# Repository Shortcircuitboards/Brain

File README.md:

# -//Brain
OSD PCB wit Sensors and usefull stuff for the FPV Rover

The Rover-Brain is complete PDB with integratetd OSD, BEC, Current Sensor, Voltage Sensor, RSSI Filter, LC Filter, and 3 Step Switch. 
It´s to keep the FPV-Rover Clean of a wire mess and to have all necessary information of your onboard system in your Video-Downlink.

I used a Mashup of the Legendary E-OSD and put some sensors and other usefull parts on one PCB. It fit´s for 2S and 3S.

The Development, Schematic and Software of the 3-Way Switch was done by JReise http://jreise.de/ (more software and Infos)
The Development, Schematic and Software of the E-OSD was done by ?? Arrgh i dont know ^^

For Setting it up You just need an USBASP to flash the OSD Firmware and the .HEX file of the AtTiny13 which is in use as an 3-Step Swicht (for flashing the pure .hex file i Use Burn-O-Mat) 
Here is the software for the attiny13: http://jreise.de/RCUSB/Daten/2-Stufen-RC-Schalter.zip  all rights by JReise !!!  Since his page is just accessible over waybackmachine.com i Uploaded the neccessary hex file to flash the attiny13

For the OSD i use the G-OSD GUI which is awseome and easy to handel !

You can manually set up the Voltage Divider with the Potentiometer P1 and the output of the Currentsensor with P2, so you can easyily adjust it to exactly that value that you need.

Pinout Legend (will be countinued later):
1 = ESC1 PWM
2 =
3 = 
4 = 
5 =
6 =
7 =
8 =
9 =
10=
11=
12=
13=
14=
15=
16=
17=
18= ESC2 PWM

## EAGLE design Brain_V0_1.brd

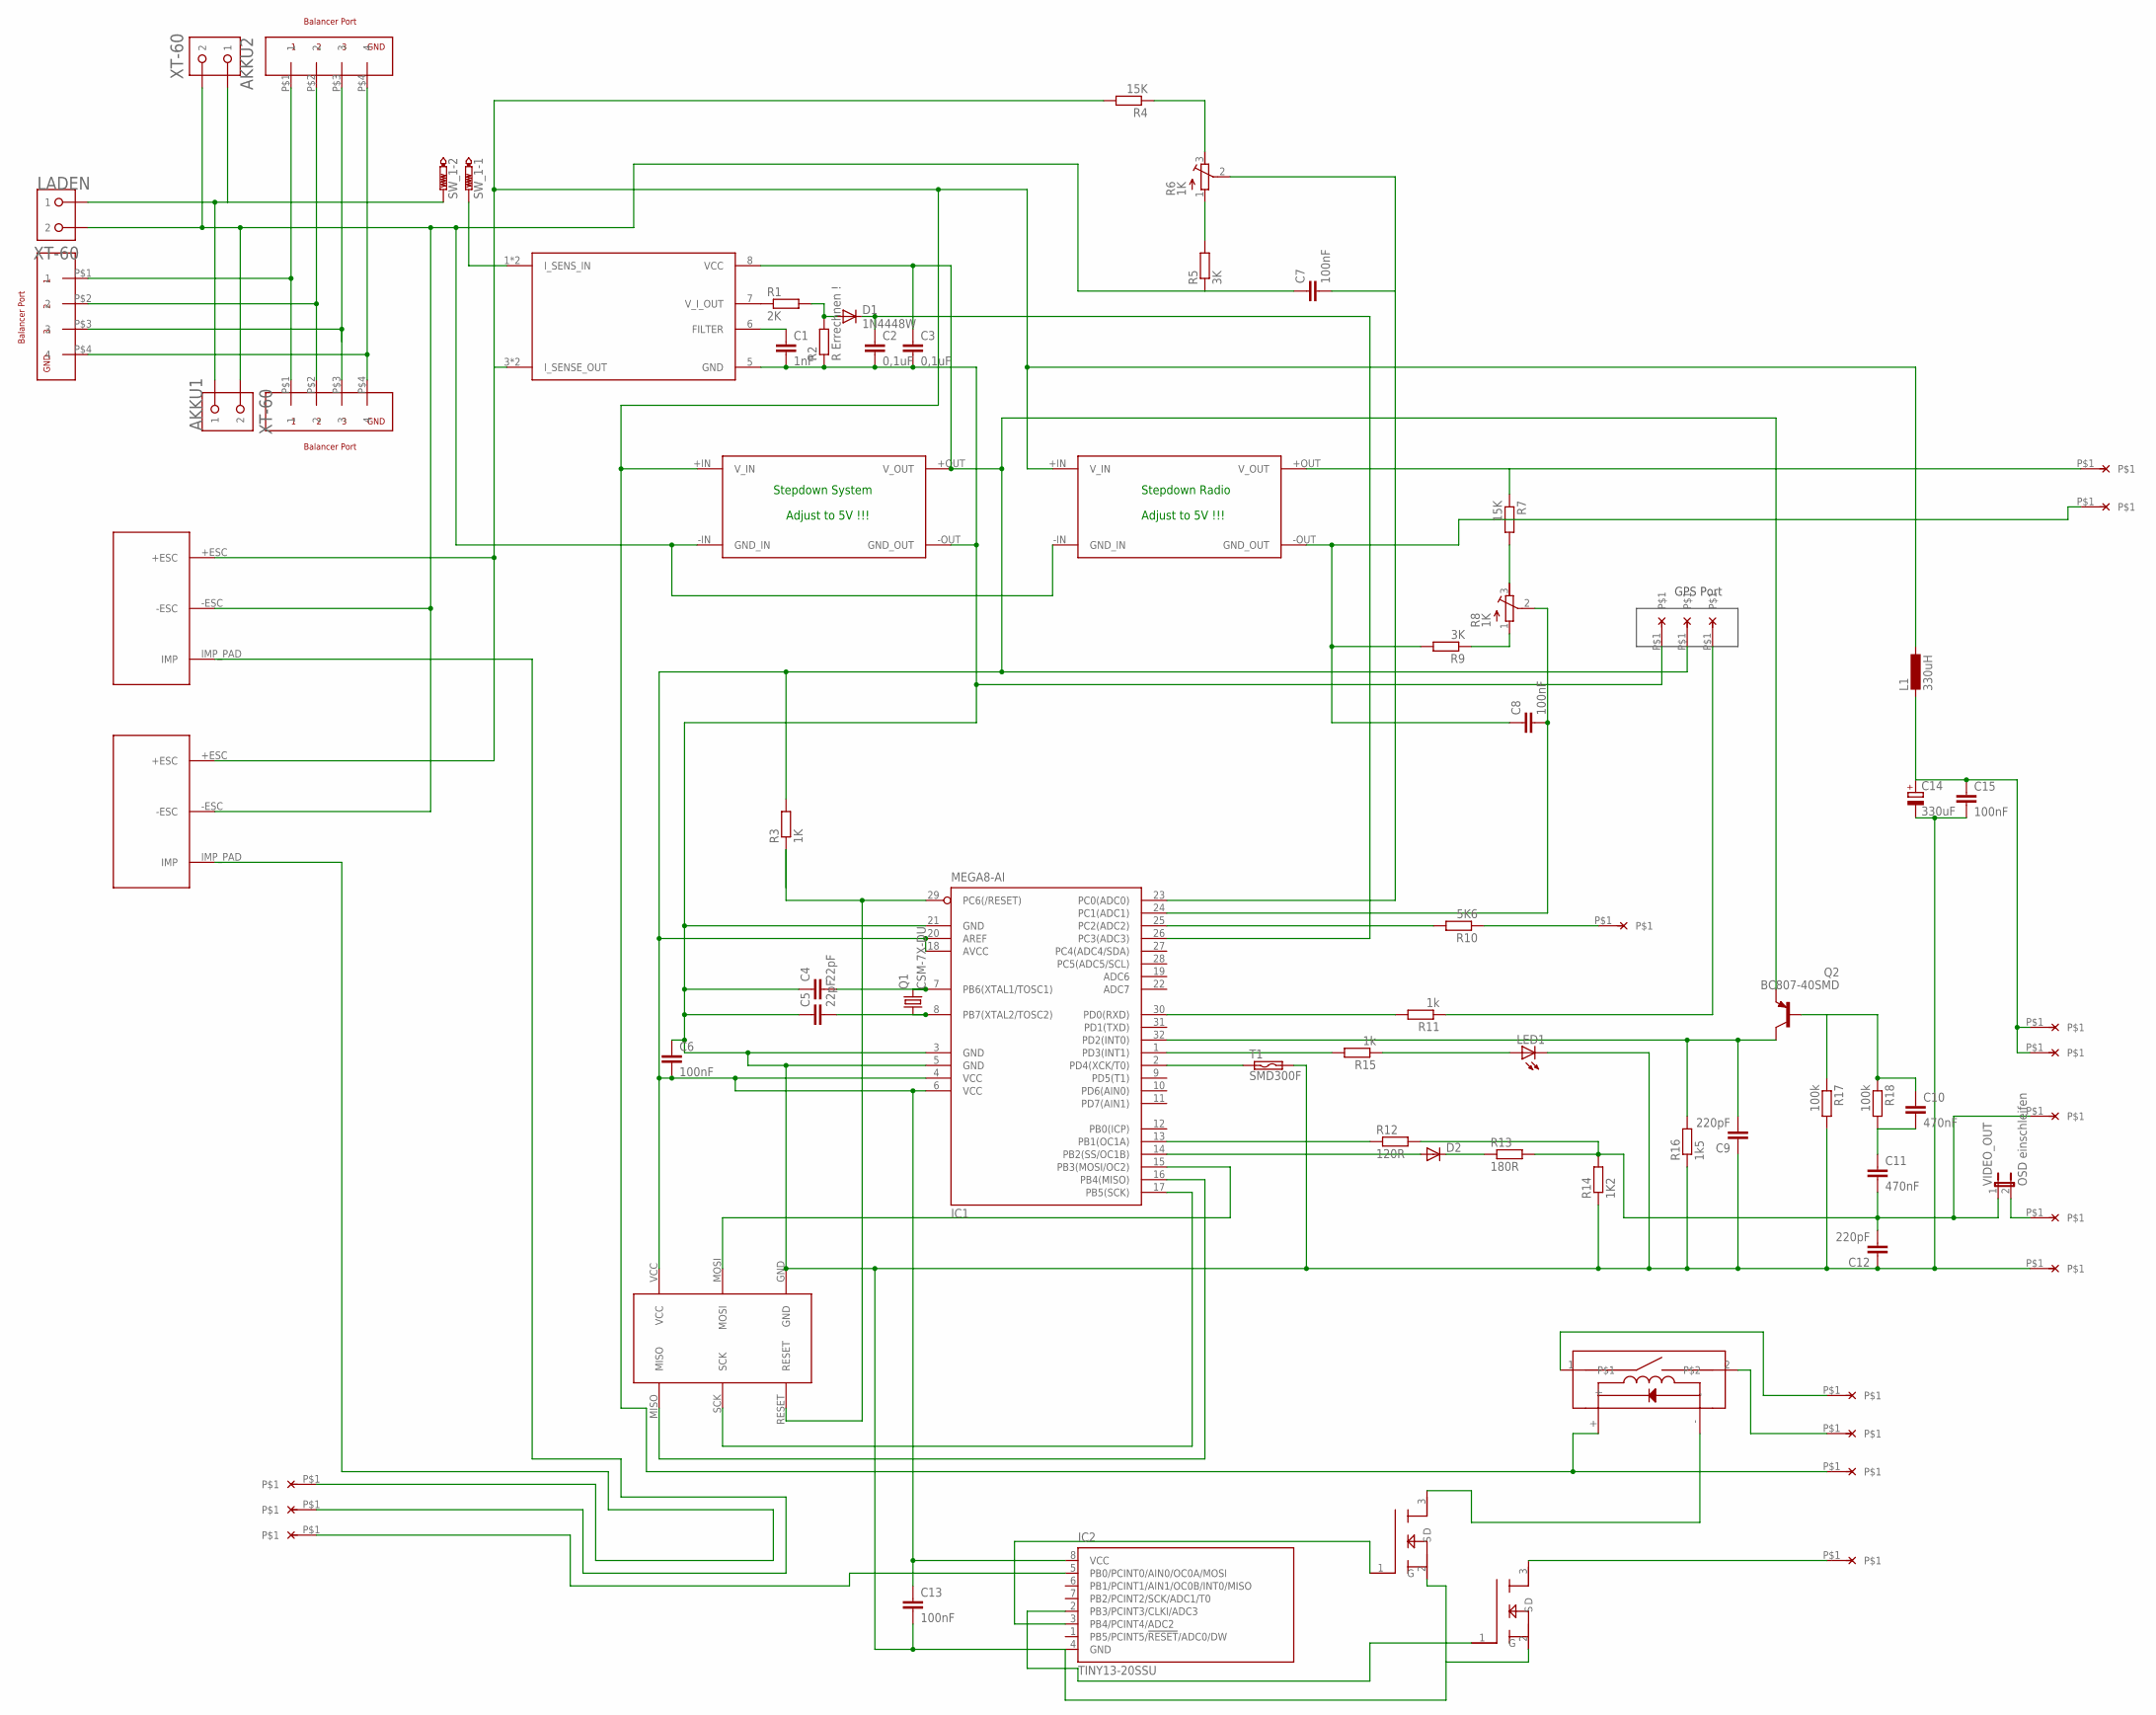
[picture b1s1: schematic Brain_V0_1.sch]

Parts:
5V_GPS: LöTPAD_KLEIN
AKKU1, AKKU2: XT-60
BALANCER_1, BALANCER_2: BALANCER_3S
BALANCE_OUT: BALANCER_3S
BEC+: LöTPAD_KLEIN
BEC-: LöTPAD_KLEIN
C1: 1nF; C0603K
C2, C3: 0,1uF; C0603K
C4, C5: 22pF; C0603K
C6, C7, C8, C13, C15: 100nF; C0603K
C9, C12: 220pF; C0603K
C10, C11: 470nF; C1206
C14: 330uF; 153CLV-0807
CAMERA_VIDEO: LöTPAD_KLEIN
CH1_IN, CH2_IN, CH3_IN: LöTPAD_KLEIN
D1: 1N4448W; SOD523
D2: DIODE-DO-214AC; DO-214AC
ESC1, ESC2: MOT_CONNECTOR
FILTER: LöTPAD_KLEIN
FILTER_: LöTPAD_KLEIN
GND_GPS: LöTPAD_KLEIN
GND_VIDEO: LöTPAD_KLEIN
IC1: MEGA8-AI; TQFP32-08
IC2: TINY13-20SSU; 8S1
IR_GND: LöTPAD_KLEIN
IR_VCC: LöTPAD_KLEIN
L1: 330uH; POWER-CHOKE_WE-TPC
LADEN: XT-60
LED1: LEDCHIP-LED0603; CHIP-LED0603
Q1: CSM-7X-DU
Q2: BC807-40SMD; SOT23-BEC
R1: 2K; R0603
R2: R Errechnen !; R0603
R3: 1K; R0603
R4, R7: 15K; R0603
R5, R9: 3K; R0603
R6, R8: 1K; RTRIM3103
R10: 5K6; R0603
R11, R15: 1k; R0603
R12: 120R; R0603
R13: 180R; R0603
R14: 1K2; R0603
R16: 1k5; R0603
R17, R18: 100k; R0603
RSSI_IN: LöTPAD_KLEIN
RX_GPS: LöTPAD_KLEIN
STEPDOWN_RADIO: STEPDOWN_MINI; STEPDOWN_SMALL
STEPDOWN_SYSTEM: STEPDOWN_MINI; STEPDOWN_SMALL
SW_1: PTR2; P2-38-17
T1: SMD300F; SMD050F
U$1: REED-RELAIS
U$2, U$5: IRLM2502; SOT23
U$3: I_SENSE_IC; SOIC8
U$4: ICSP_6P
VCC_CAM: LöTPAD_KLEIN
VCC_VTX: LöTPAD_KLEIN
VIDEO: LöTPAD_KLEIN
VIDEO_OUT: OSD einschleifen; JP1

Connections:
unnamed: AKKU1.BATT (1), AKKU2.BATT (1), LADEN.BATT (1), SW_1.TP-2
unnamed: AKKU1.GND (2), AKKU2.GND (2), C7.1, ESC1.-ESC, ESC2.-ESC, LADEN.GND (2), R5.1, STEPDOWN_RADIO.-IN (GND_IN), STEPDOWN_SYSTEM.-IN (GND_IN)
unnamed: BALANCER_1.P$1 (1), BALANCER_2.P$1 (1), BALANCE_OUT.P$1 (1)
unnamed: BALANCER_1.P$2 (2), BALANCER_2.P$2 (2), BALANCE_OUT.P$2 (2)
unnamed: BALANCER_1.P$4 (4), BALANCER_2.P$4 (4), BALANCE_OUT.P$4 (4)
unnamed: SW_1.TP-1, U$3.1 (I_SENS_IN), U$3.2 (I_SENS_IN)
unnamed: 5V_GPS.P$1, C3.1, C6.2, C13.1, IC1.4 (VCC), IC1.6 (VCC), IC1.18 (AVCC), IC1.20 (AREF), IC2.8 (VCC), Q2.E, R3.2, STEPDOWN_SYSTEM.+OUT (V_OUT), U$3.8 (VCC), U$4.VCC
unnamed: C4.2, IC1.7 (PB6(XTAL1/TOSC1)), Q1.2
unnamed: C1.1, U$3.6 (FILTER)
unnamed: R1.1, U$3.7 (V_I_OUT)
unnamed: D1.A, R1.2, R2.2
unnamed: C2.1, D1.C, IC1.26 (PC3(ADC3))
unnamed: FILTER_.P$1, U$1.2
unnamed: C5.2, IC1.8 (PB7(XTAL2/TOSC2)), Q1.1
unnamed: IC1.29 (PC6(/RESET)), R3.1, U$4.RESET
unnamed: IC1.15 (PB3(MOSI/OC2)), U$4.MOSI
unnamed: IC1.17 (PB5(SCK)), U$4.SCK
unnamed: R4.1, R6.3 (E)
unnamed: IC1.16 (PB4(MISO)), U$4.MISO
unnamed: R5.2, R6.1 (A)
unnamed: VIDEO.P$1, VIDEO_OUT.2
unnamed: C7.2, IC1.23 (PC0(ADC0)), R6.2 (S)
unnamed: R7.2, R8.3 (E)
unnamed: R8.1 (A), R9.1
unnamed: BEC-.P$1, C8.1, R9.2, STEPDOWN_RADIO.-OUT (GND_OUT)
unnamed: C8.2, IC1.24 (PC1(ADC1)), R8.2 (S)
unnamed: IC1.25 (PC2(ADC2)), R10.2
unnamed: R10.1, RSSI_IN.P$1
unnamed: IC1.30 (PD0(RXD)), R11.2
unnamed: R11.1, RX_GPS.P$1
unnamed: IC1.2 (PD4(XCK/T0)), T1.1
unnamed: IC1.13 (PB1(OC1A)), R12.1
unnamed: C11.2, C12.2, CAMERA_VIDEO.P$1, R12.2, R13.2, R14.2, VIDEO_OUT.1
unnamed: D2.A, IC1.14 (PB2(SS/OC1B))
unnamed: D2.C, R13.1
unnamed: IC1.1 (PD3(INT1)), R15.2
unnamed: LED1.A, R15.1
unnamed: CH1_IN.P$1, ESC2.IMP_PAD (IMP)
unnamed: CH2_IN.P$1, ESC1.IMP_PAD (IMP)
unnamed: CH3_IN.P$1, IC2.5 (PB0/PCINT0/AIN0/OC0A/MOSI)
unnamed: FILTER.P$1, U$1.1
unnamed: ESC1.+ESC, ESC2.+ESC, IR_VCC.P$1, L1.1, R4.2, STEPDOWN_RADIO.+IN (V_IN), STEPDOWN_SYSTEM.+IN (V_IN), U$1.+, U$3.3 (I_SENSE_OUT), U$3.4 (I_SENSE_OUT)
unnamed: C9.2, IC1.32 (PD2(INT0)), Q2.C, R16.2
unnamed: C10.1, Q2.B, R17.1, R18.1
unnamed: BALANCER_1.P$3 (3), BALANCER_2.P$3 (3), BALANCE_OUT.P$3 (3)
unnamed: C10.2, C11.1, R18.2
unnamed: IC2.3 (PB4/PCINT4/ADC2), U$2.1 (G)
unnamed: IC2.2 (PB3/PCINT3/CLKI/ADC3), U$5.1 (G)
unnamed: U$1.-, U$2.3 (D)
unnamed: IR_GND.P$1, U$5.3 (D)
unnamed: BEC+.P$1, R7.1, STEPDOWN_RADIO.+OUT (V_OUT)
unnamed: C14.+, C15.1, L1.2, VCC_CAM.P$1, VCC_VTX.P$1
unnamed: C1.2, C2.2, C3.2, C4.1, C5.1, C6.1, C9.1, C12.1, C13.2, C14.-, C15.2, GND_GPS.P$1, GND_VIDEO.P$1, IC1.3 (GND), IC1.5 (GND), IC1.21 (GND), IC2.4 (GND), LED1.C, R2.1, R14.1, R16.1, R17.2, STEPDOWN_SYSTEM.-OUT (GND_OUT), T1.2, U$2.2 (S), U$3.5 (GND), U$4.GND, U$5.2 (S)

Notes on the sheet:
Stepdown System
Stepdown Radio
Adjust to 5V !!!
GPS Port

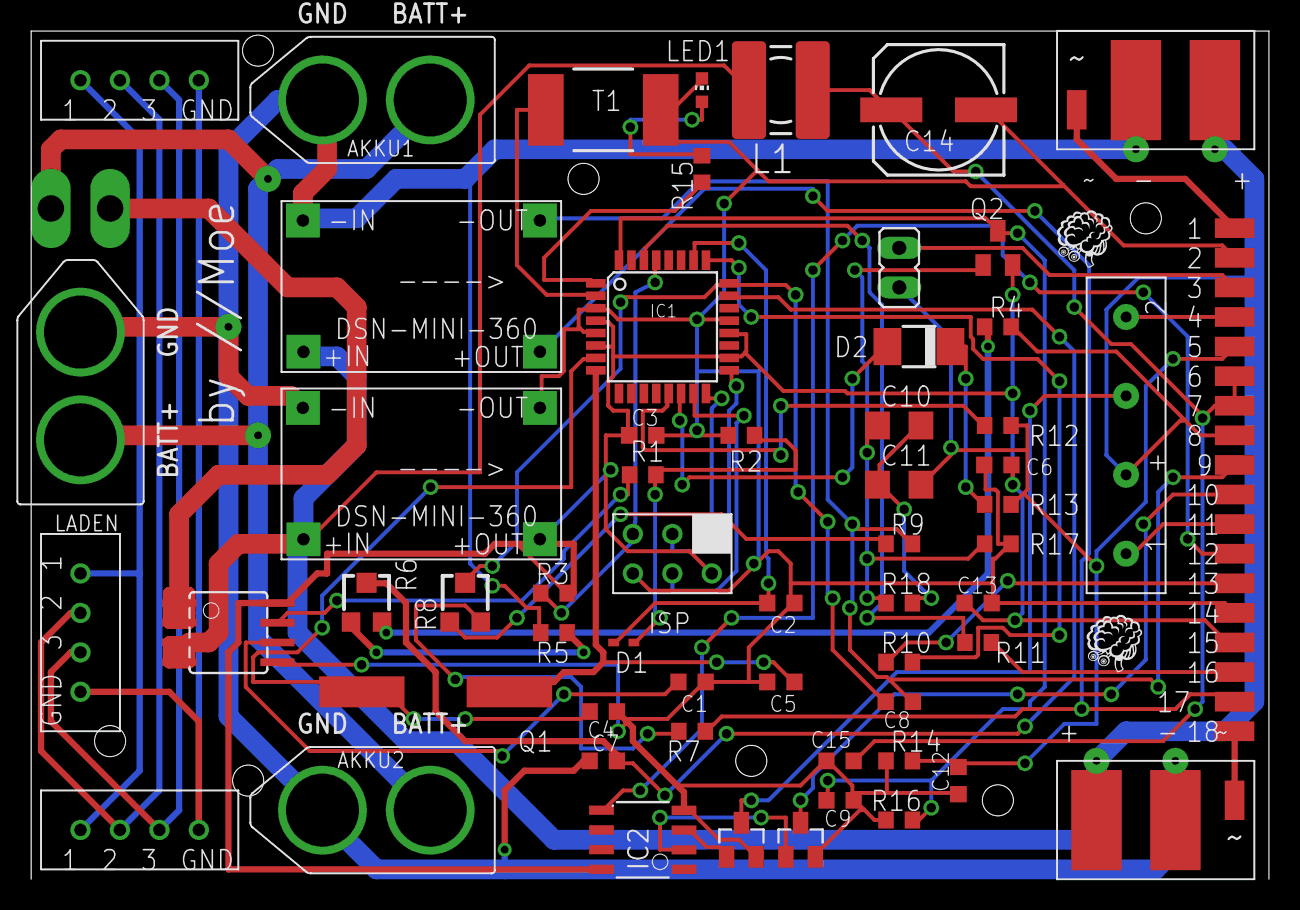
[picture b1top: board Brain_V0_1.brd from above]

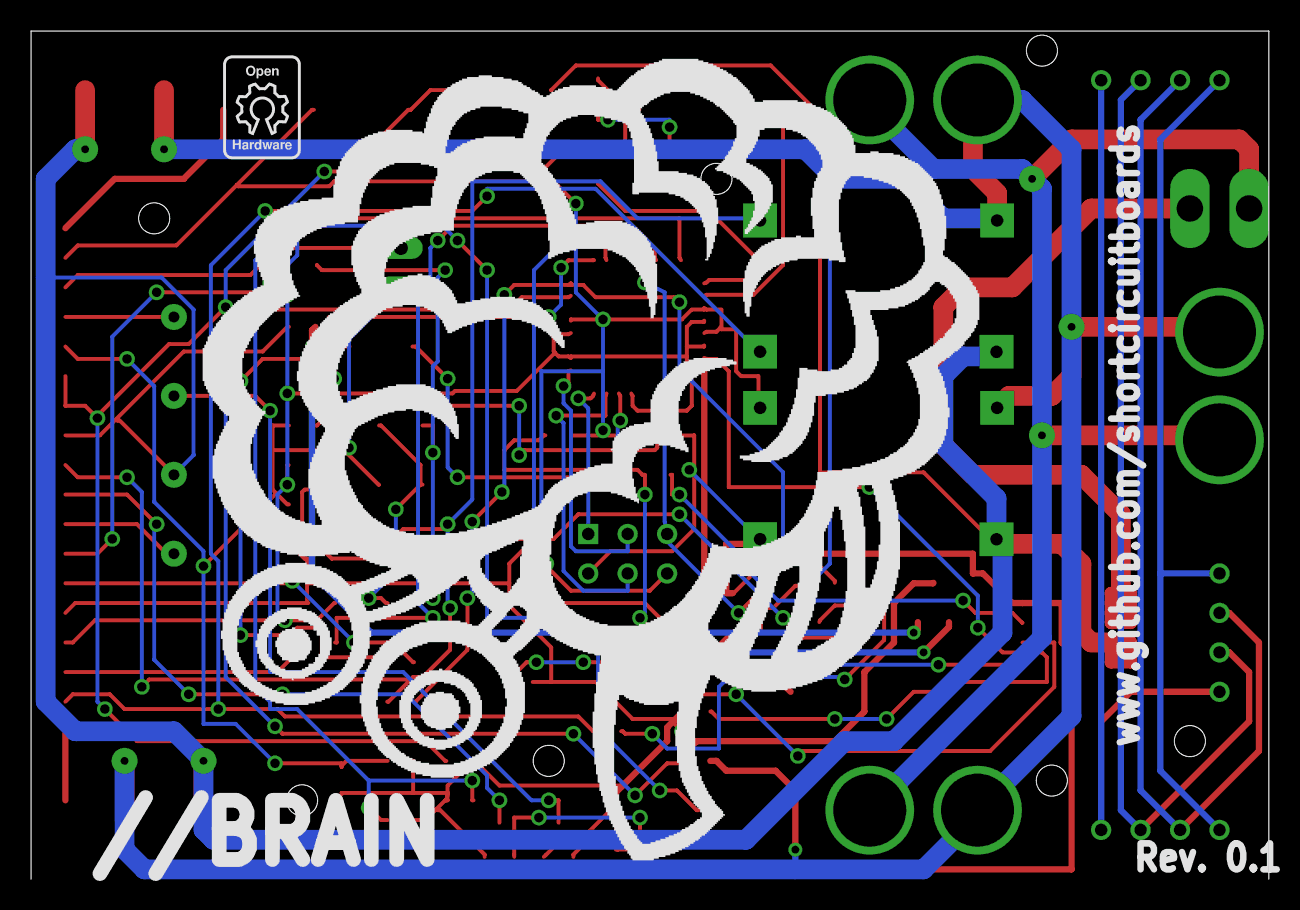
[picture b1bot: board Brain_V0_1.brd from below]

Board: 2 copper layers, 79.7 x 54.6 mm, 81 parts (2 on the bottom side), 53 nets.

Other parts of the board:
E$1, E$2: BRAINLOGO
E$3: BRAINLOGO_BIG
E$4: OPEN_HARDWARE_SMALL

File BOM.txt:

Partlist

Exported from Brain_V0_1.brd at 12.01.2016 13:22:20

EAGLE Version 6.3.0 Copyright (c) 1988-2012 CadSoft

Assembly variant: 

Part            Value            Package            Library                Position (mm)         Orientation


AKKU1           XT-60            XT-60              RoboJackets-Connectors (29.845 75.565)       R90
AKKU2           XT-60            XT-60              RoboJackets-Connectors (29.845 29.845)       R90
C1              1nF              C0603K             resistor               (42.545 38.1)         R0
C2              0,1uF            C0603K             resistor               (48.26 43.18)         R0
C3              0,1uF            C0603K             resistor               (39.37 53.975)        R0
C4              22pF             C0603K             rcl                    (36.83 36.195)        R180
C5              22pF             C0603K             rcl                    (48.26 38.1)          R0
C6              100nF            C0603K             rcl                    (62.23 52.07)         R0
C7              100nF            C0603K             rcl                    (36.83 33.02)         R0
C8              100nF            C0603K             rcl                    (55.88 36.83)         R180
C9              220pF            C0603K             rcl                    (52.07 30.48)         R180
C10             470nF            C1206              rcl                    (55.88 54.61)         R0
C11             470nF            C1206              rcl                    (55.88 50.8)          R0
C12             220pF            C0603K             rcl                    (59.69 31.75)         R90
C13             100nF            C0603K             rcl                    (60.96 43.18)         R0
C14             330uF            153CLV-0807        rcl                    (58.42 74.93)         R180
C15             100nF            C0603K             rcl                    (52.07 33.02)         R180
D1              1N4448W          SOD523             diode                  (38.1 40.64)          R0
D2                               DO-214AC           diode                  (57.15 59.69)         R180
IC1             MEGA8-AI         TQFP32-08          atmel                  (40.64 60.96)         R0
IC2             TINY13-20SSU     8S1                atmel                  (39.37 27.94)         R90
L1              330uH            POWER-CHOKE_WE-TPC rcl                    (48.26 76.2)          R90
LADEN           XT-60            XT-60              RoboJackets-Connectors (3.175 49.53)         R0
LED1                             CHIP-LED0603       led                    (43.18 76.2)          R0
Q1              CSM-7X-DU        CSM-7X-DU          crystal 16 mhz               (26.035 37.465)       R180
Q2              BC807-40SMD      SOT23-BEC          transistor-pnp         (62.23 66.04)         R0
R1              2K               R0603              resistor               (39.37 51.435)        R0
R2              R Errechnen !    R0603              resistor               (45.72 53.975)        R0
R3              1K               R0603              rcl                    (33.655 43.815)       R0
R4              15K              R0603              rcl                    (62.23 60.96)         R0
R5              3K               R0603              rcl                    (33.655 41.275)       R0
R6              1K               RTRIM3103          rcl                    (21.59 43.18)         R0
R7              15K              R0603              rcl                    (42.545 34.925)       R180
R8              1K               RTRIM3103          rcl                    (27.94 43.18)         R0
R9              3K               R0603              rcl                    (55.88 46.99)         R0
R10             5K6              R0603              rcl                    (55.88 39.37)         R0
R11             1k               R0603              rcl                    (60.96 40.64)         R180
R12             120R             R0603              rcl                    (62.23 54.61)         R0
R13             180R             R0603              rcl                    (62.23 49.53)         R0
R14             1K2              R0603              rcl                    (55.88 33.02)         R0
R15             1k               R0603              rcl                    (43.18 71.12)         R270
R16             1k5              R0603              rcl                    (55.88 29.21)         R0
R17             100k             R0603              rcl                    (62.23 46.99)         R0
R18             100k             R0603              rcl                    (55.88 43.18)         R0
SW_1            PTR2             P2-38-17           testpad                (3.175 68.58)         R180
T1              SMD300F          SMD050F            switch-raychem         (36.83 74.93)         R0
U$1             REED-RELAIS      REED-RELAIS        				       (70.485 53.975)       R90
U$2             IRLM2502         SOT23              				       (45.72 27.94)         R0
U$3             I_SENSE_IC       SOIC8              				       (12.7 41.275)         R270
U$4             ICSP_6P          ICSP_6P            				       (43.815 48.895)       R180
U$5             IRLM2502         SOT23              				       (49.53 27.94)         R0
VIDEO_OUT       OSD einschleifen JP1                jumper                 (55.88 64.77)         R0

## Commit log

2016-01-14 Eagle PCB Files
    Here are the files for the V0_1
